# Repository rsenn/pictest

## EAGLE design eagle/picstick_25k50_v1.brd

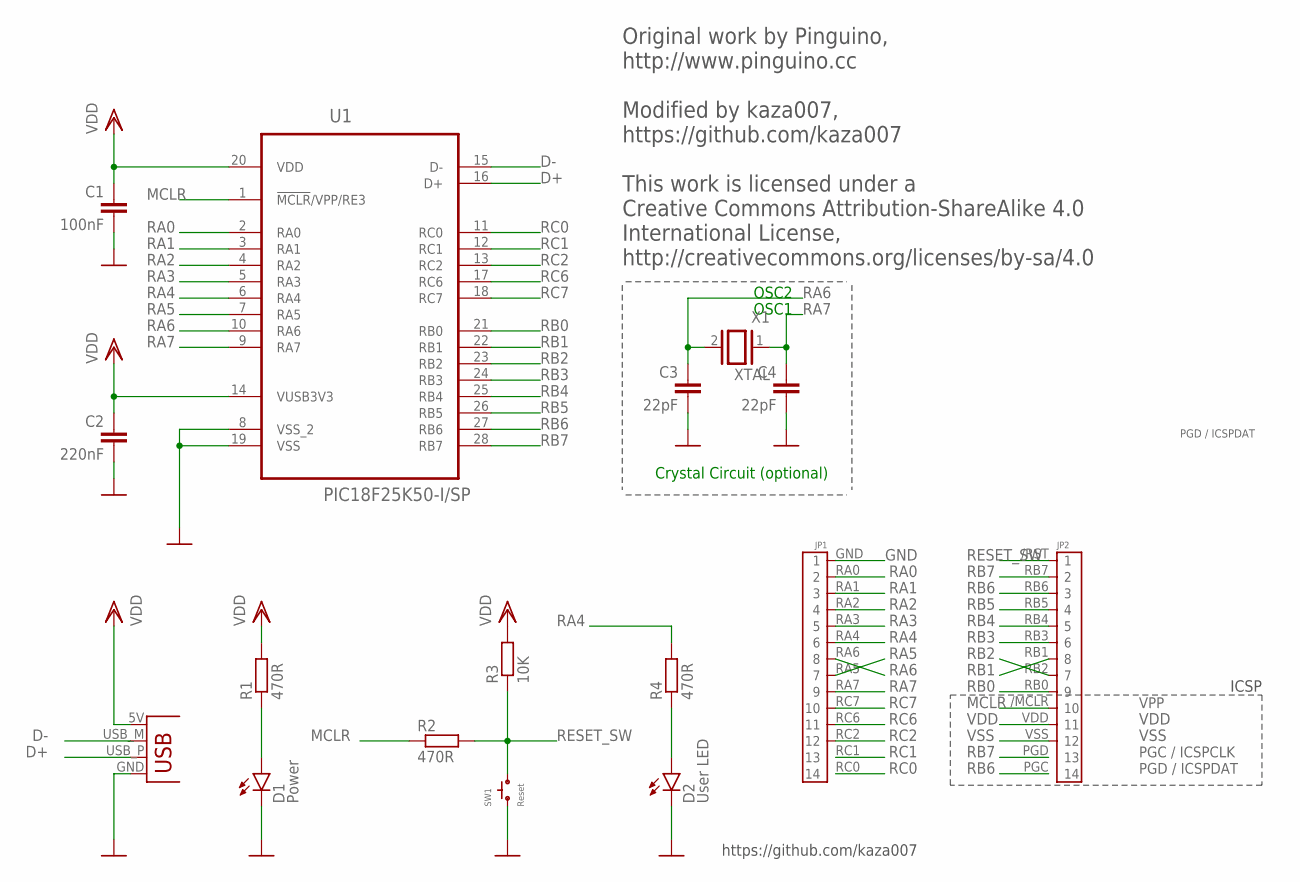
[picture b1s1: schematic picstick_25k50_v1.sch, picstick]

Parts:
C1: 100nF; C050-024X044
C2: 220nF; C050-024X044
C3, C4: 22pF; C025-024X044
D1: Power; LED3MM
D2: User LED; LED3MM
JP1: CONN-14P-PICSTICK-JP1; PICSTICK_JP1
JP2: CONN-14P-PICSTICK-JP2; PICSTICK_JP2
R1, R2, R4: 470R; 0204/7
R3: 10K; 0204/7
SW1: Reset; SKHLAAA010
U1: PIC18F25K50-I/SP; DIP254P762X406-28P
USB: FREETRONICS-MASTER-V1_USBPCB; FREETRONICS-MASTER-V1_USB-A-PCB
X1: XTAL; QS

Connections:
D+: U1.16 (D+), USB.USB_P (D+)
D-: U1.15 (D-), USB.USB_M (D-)
GND: C1.2, C2.2, C3.2, C4.2, D1.K (C), D2.K (C), JP1.GND (1), SW1.1, U1.8 (VSS_2), U1.19 (VSS), USB.GND
MCLR: JP2./MCLR (10), R2.1, U1.1 (!MCLR!/VPP/RE3)
unnamed: D1.A, R1.1
unnamed: D2.A, R4.1
RA0: JP1.RA0 (2), U1.2 (RA0)
RA1: JP1.RA1 (3), U1.3 (RA1)
RA2: JP1.RA2 (4), U1.4 (RA2)
RA3: JP1.RA3 (5), U1.5 (RA3)
RA4: JP1.RA4 (6), R4.2, U1.6 (RA4)
RA5: JP1.RA5 (7), U1.7 (RA5)
RA6: C3.1, JP1.RA6 (8), U1.10 (RA6), X1.2
RA7: C4.1, JP1.RA7 (9), U1.9 (RA7), X1.1
RB0: JP2.RB0 (9), U1.21 (RB0)
RB1: JP2.RB1 (8), U1.22 (RB1)
RB2: JP2.RB2 (7), U1.23 (RB2)
RB3: JP2.RB3 (6), U1.24 (RB3)
RB4: JP2.RB4 (5), U1.25 (RB4)
RB5: JP2.RB5 (4), U1.26 (RB5)
RB6: JP2.PGC (14), JP2.RB6 (3), U1.27 (RB6)
RB7: JP2.PGD (13), JP2.RB7 (2), U1.28 (RB7)
RC0: JP1.RC0 (14), U1.11 (RC0)
RC1: JP1.RC1 (13), U1.12 (RC1)
RC2: JP1.RC2 (12), U1.13 (RC2)
RC6: JP1.RC6 (11), U1.17 (RC6)
RC7: JP1.RC7 (10), U1.18 (RC7)
RESET_SW: JP2./RST (1), R2.2, R3.1, SW1.2
VDD: C1.1, C2.1, JP2.VDD (11), R1.2, R3.2, U1.14 (VUSB3V3), U1.20 (VDD), USB.5V (VBUS)
VSS: JP2.VSS (12)

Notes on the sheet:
ICSP
Crystal Circuit (optional)
OSC2
OSC1
https://github.com/kaza007
Original work by Pinguino, http://www.pinguino.cc Modified by kaza007, https://github.com/kaza007 This work is licensed under a Creative Commons Attribution-ShareAlike 4.0 International License, http://creativecommons.org/licenses/by-sa/4.0
PGD / ICSPDAT
PGC / ICSPCLK
VPP

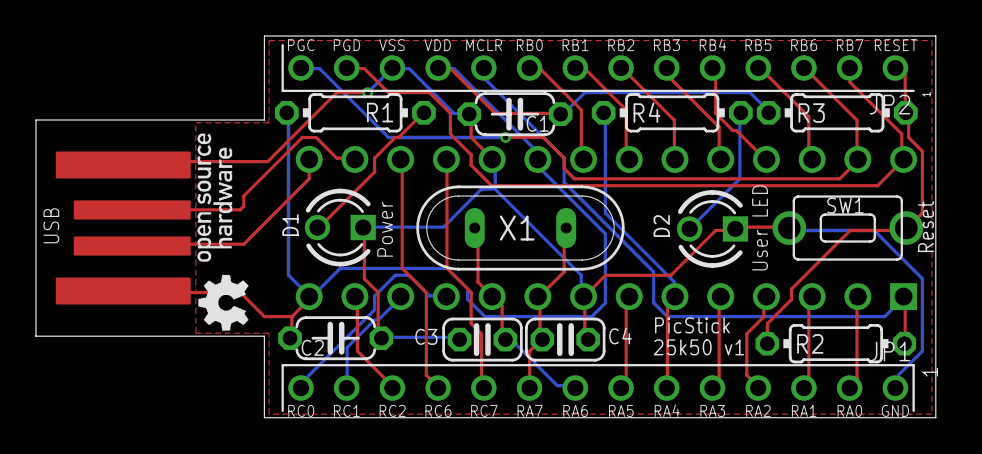
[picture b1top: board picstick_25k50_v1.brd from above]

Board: 2 copper layers, 50.0 x 21.2 mm, 16 parts (1 on the bottom side), 29 nets.

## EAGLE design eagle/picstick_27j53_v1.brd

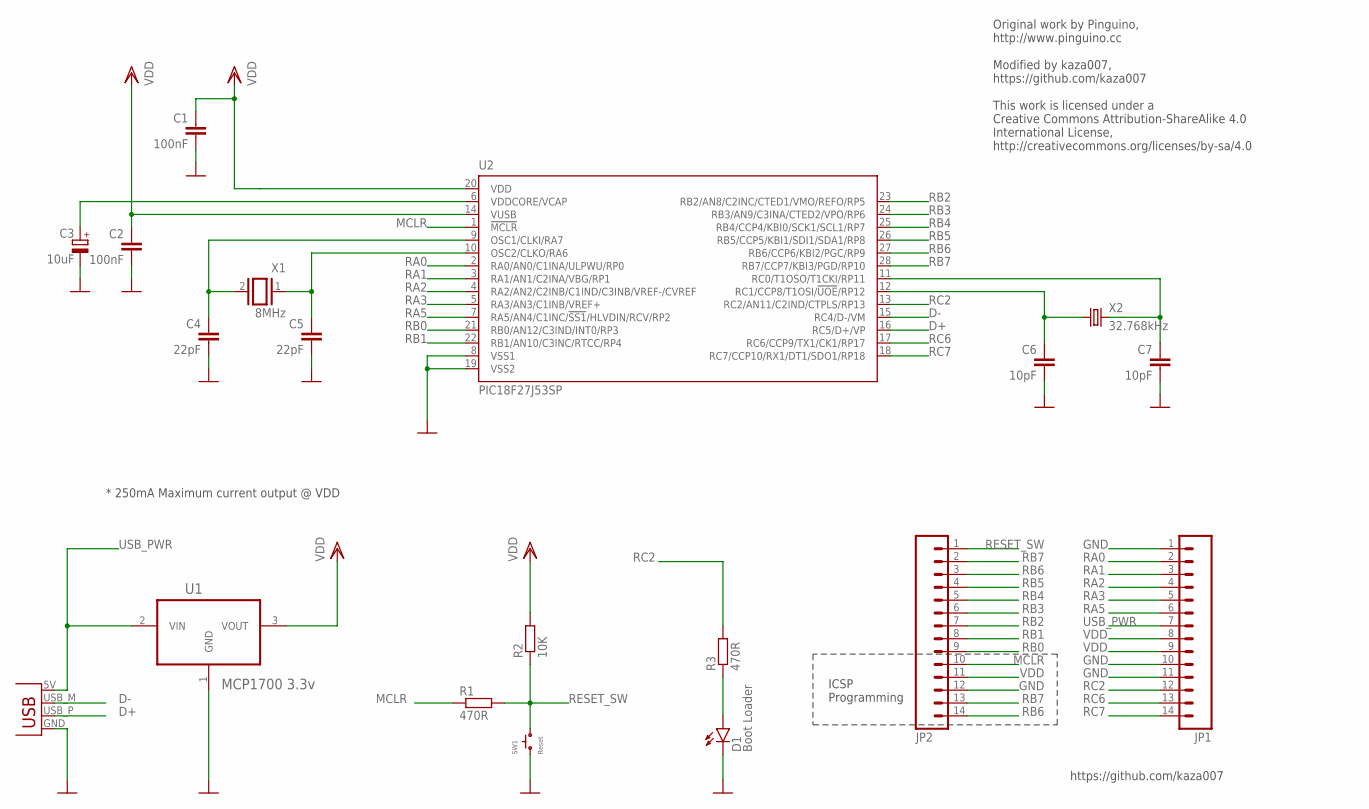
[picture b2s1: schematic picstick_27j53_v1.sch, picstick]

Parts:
C1, C2: 100nF; C050-024X044
C3: 10uF; E2,5-5
C4, C5: 22pF; C025-024X044
C6, C7: 10pF; C025-024X044
D1: Boot Loader; LED3MM
JP1, JP2: FREETRONICS-JON_M14; FREETRONICS-JON_1X14
R1, R3: 470R; 0204/7
R2: 10K; 0204/7
SW1: Reset; SKHLAAA010
U1: MCP1700 3.3v; TO127P254X495-3
U2: PIC18F27J53SP; DIL28-3
USB: FREETRONICS-MASTER-V1_USBPCB; FREETRONICS-MASTER-V1_USB-A-PCB
X1: 8MHz; QS
X2: 32.768kHz; TC26H

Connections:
D+: U2.16 (RC5/D+/VP), USB.USB_P (D+)
D-: U2.15 (RC4/D-/VM), USB.USB_M (D-)
GND: C1.2, C2.2, C3.-, C4.2, C5.2, C6.2, C7.2, D1.K (C), JP1.1, JP1.10, JP1.11, JP2.12, SW1.1, U1.1 (GND), U2.8 (VSS1), U2.19 (VSS2), USB.GND
MCLR: JP2.10, R1.1, U2.1 (!MCLR)
unnamed: C4.1, U2.9 (OSC1/CLKI/RA7), X1.2
unnamed: C5.1, U2.10 (OSC2/CLKO/RA6), X1.1
unnamed: C3.+, U2.6 (VDDCORE/VCAP)
unnamed: C7.1, U2.11 (RC0/T1OSO/T1CKI/RP11), X2.2
unnamed: C6.1, U2.12 (RC1/CCP8/T1OSI/!UOE!/RP12), X2.1
unnamed: D1.A, R3.1
RA0: JP1.2, U2.2 (RA0/AN0/C1INA/ULPWU/RP0)
RA1: JP1.3, U2.3 (RA1/AN1/C2INA/VBG/RP1)
RA2: JP1.4, U2.4 (RA2/AN2/C2INB/C1IND/C3INB/VREF-/CVREF)
RA3: JP1.5, U2.5 (RA3/AN3/C1INB/VREF+)
RA5: JP1.6, U2.7 (RA5/AN4/C1INC/!SS1!/HLVDIN/RCV/RP2)
RB0: JP2.9, U2.21 (RB0/AN12/C3IND/INT0/RP3)
RB1: JP2.8, U2.22 (RB1/AN10/C3INC/RTCC/RP4)
RB2: JP2.7, U2.23 (RB2/AN8/C2INC/CTED1/VMO/REFO/RP5)
RB3: JP2.6, U2.24 (RB3/AN9/C3INA/CTED2/VPO/RP6)
RB4: JP2.5, U2.25 (RB4/CCP4/KBI0/SCK1/SCL1/RP7)
RB5: JP2.4, U2.26 (RB5/CCP5/KBI1/SDI1/SDA1/RP8)
RB6: JP2.3, JP2.14, U2.27 (RB6/CCP6/KBI2/PGC/RP9)
RB7: JP2.2, JP2.13, U2.28 (RB7/CCP7/KBI3/PGD/RP10)
RC2: JP1.12, R3.2, U2.13 (RC2/AN11/C2IND/CTPLS/RP13)
RC6: JP1.13, U2.17 (RC6/CCP9/TX1/CK1/RP17)
RC7: JP1.14, U2.18 (RC7/CCP10/RX1/DT1/SDO1/RP18)
RESET_SW: JP2.1, R1.2, R2.1, SW1.2
USB_PWR: JP1.7, U1.2 (VIN), USB.5V (VBUS)
VDD: C1.1, C2.1, JP1.8, JP1.9, JP2.11, R2.2, U1.3 (VOUT), U2.14 (VUSB), U2.20 (VDD)

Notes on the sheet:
ICSP Programming
* 250mA Maximum current output @ VDD
https://github.com/kaza007
Original work by Pinguino, http://www.pinguino.cc Modified by kaza007, https://github.com/kaza007 This work is licensed under a Creative Commons Attribution-ShareAlike 4.0 International License, http://creativecommons.org/licenses/by-sa/4.0

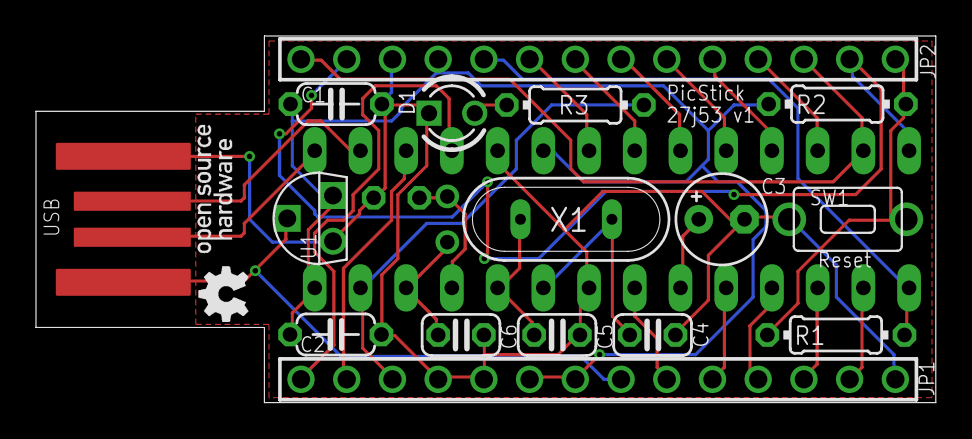
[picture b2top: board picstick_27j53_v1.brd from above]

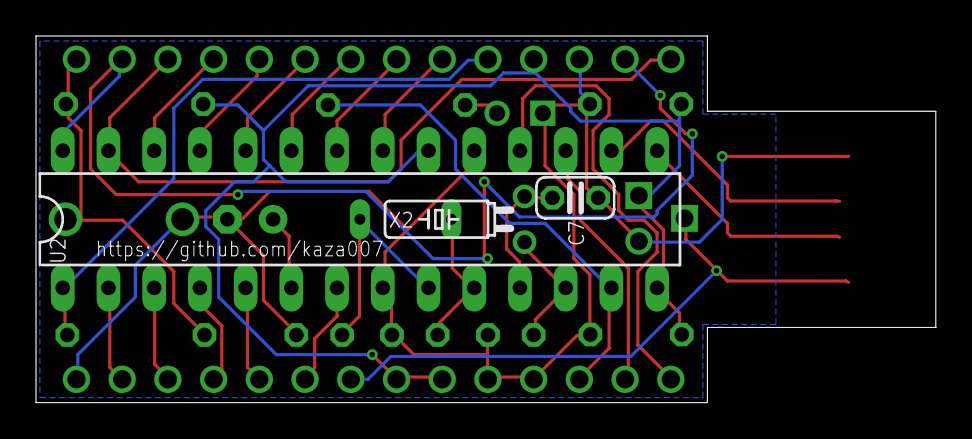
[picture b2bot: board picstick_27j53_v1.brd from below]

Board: 2 copper layers, 50.0 x 20.4 mm, 19 parts (3 on the bottom side), 29 nets.

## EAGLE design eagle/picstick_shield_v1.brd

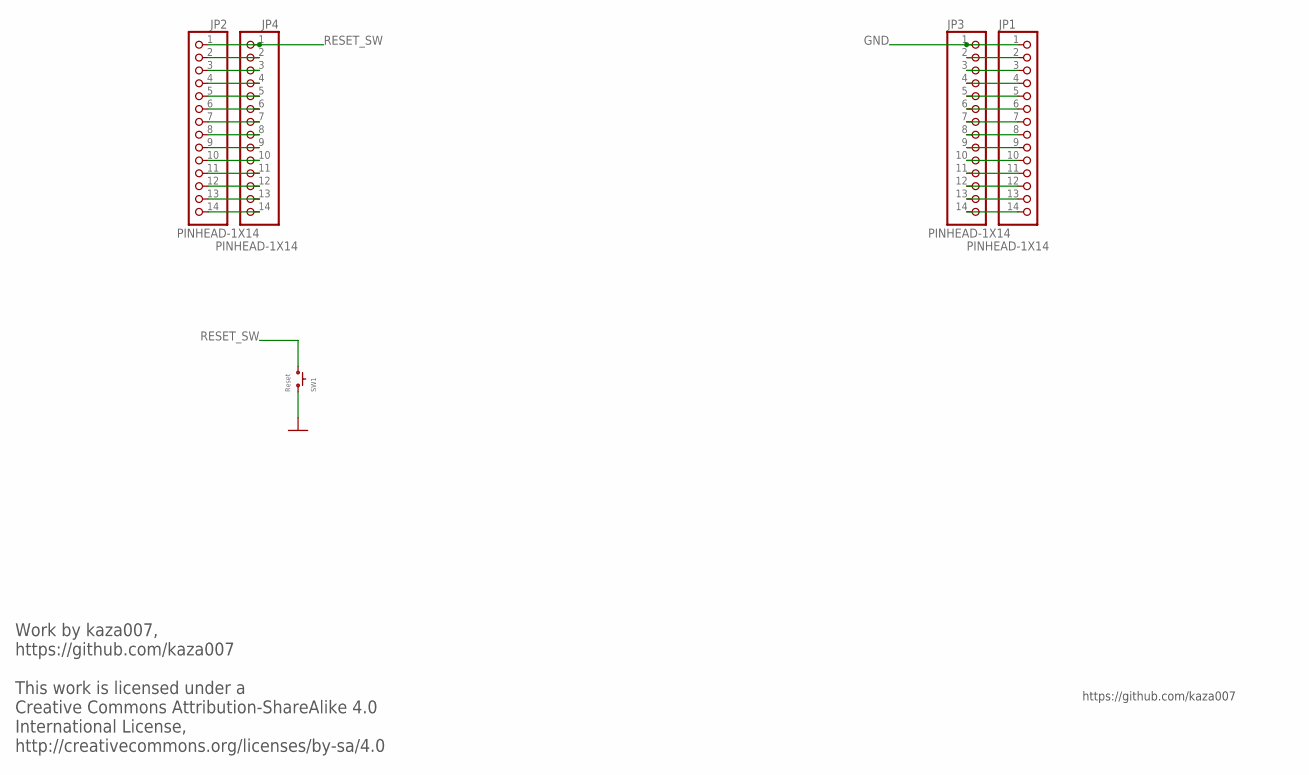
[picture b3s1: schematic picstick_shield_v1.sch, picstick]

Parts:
JP1, JP2, JP3, JP4: PINHEAD-1X14
SW1: Reset; SKHLAAA010

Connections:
GND: JP1.1, JP3.1, SW1.1
unnamed: JP1.2, JP3.2
unnamed: JP2.7, JP4.7
unnamed: JP2.8, JP4.8
unnamed: JP2.9, JP4.9
unnamed: JP2.10, JP4.10
unnamed: JP2.11, JP4.11
unnamed: JP2.12, JP4.12
unnamed: JP2.13, JP4.13
unnamed: JP2.14, JP4.14
unnamed: JP1.3, JP3.3
unnamed: JP1.4, JP3.4
unnamed: JP1.5, JP3.5
unnamed: JP1.6, JP3.6
unnamed: JP1.7, JP3.7
unnamed: JP1.8, JP3.8
unnamed: JP1.9, JP3.9
unnamed: JP1.10, JP3.10
unnamed: JP1.11, JP3.11
unnamed: JP1.12, JP3.12
unnamed: JP1.13, JP3.13
unnamed: JP1.14, JP3.14
RB2: JP2.6, JP4.6
RB3: JP2.5, JP4.5
RB4: JP2.4, JP4.4
RB5: JP2.3, JP4.3
RB6: JP2.2, JP4.2
RESET_SW: JP2.1, JP4.1, SW1.2

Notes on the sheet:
https://github.com/kaza007
Work by kaza007, https://github.com/kaza007 This work is licensed under a Creative Commons Attribution-ShareAlike 4.0 International License, http://creativecommons.org/licenses/by-sa/4.0

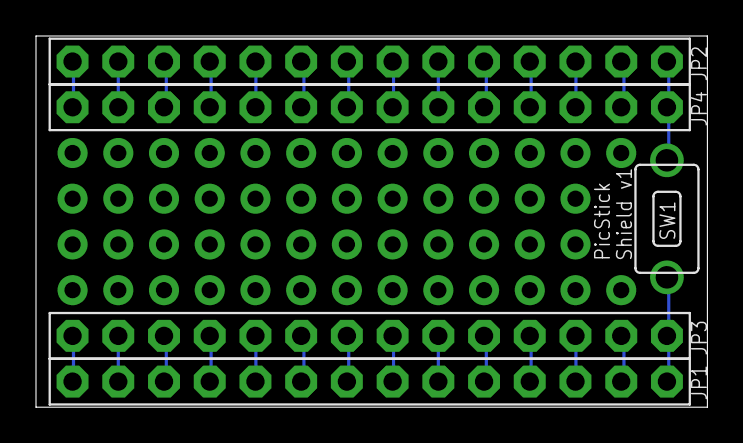
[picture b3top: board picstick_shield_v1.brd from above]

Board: 2 copper layers, 37.3 x 20.6 mm, 5 parts (0 on the bottom side), 28 nets.

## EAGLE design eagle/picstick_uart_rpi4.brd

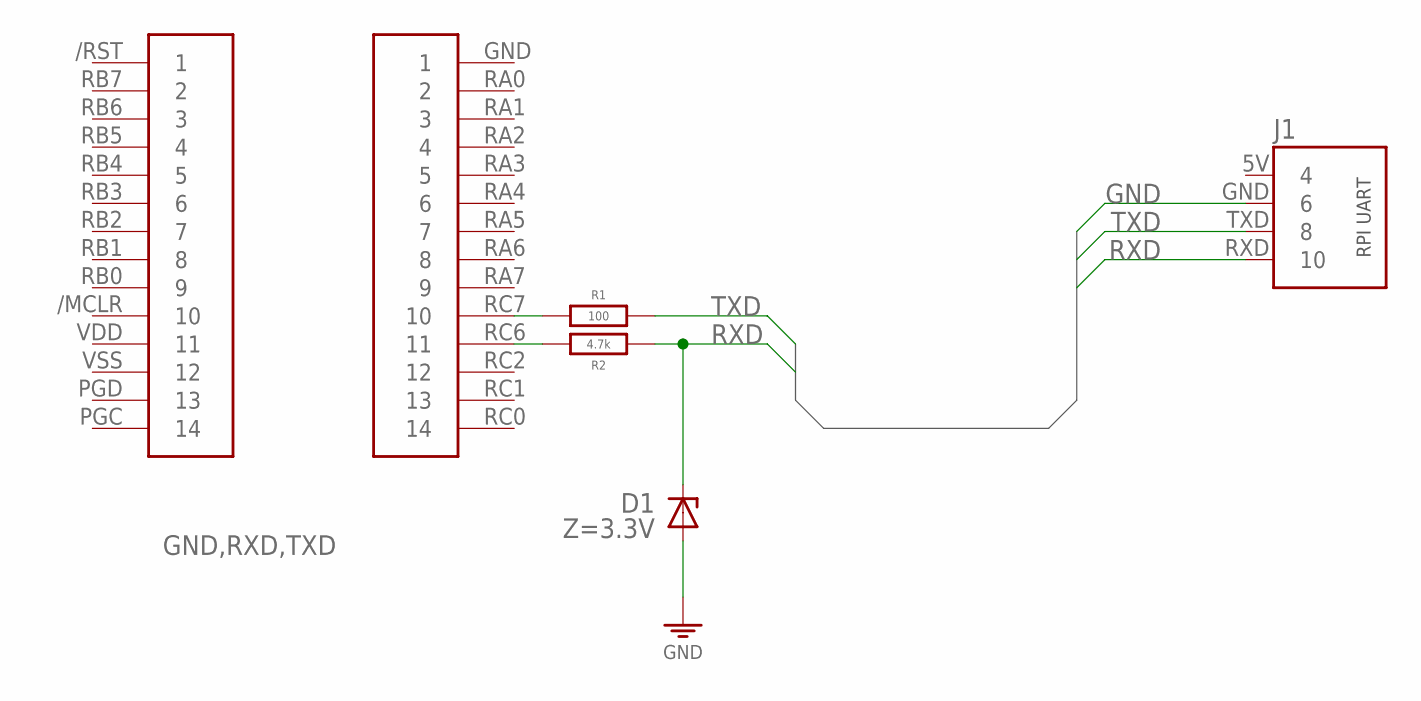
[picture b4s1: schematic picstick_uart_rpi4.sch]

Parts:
D1: Z=3.3V; DO34Z10
J1: RPI-UART-RPI4; RPI-UART
J2: PICSTICK; PICSTICK_ALT
R1: 100; 0204/12
R2: 4.7k; 0204/12

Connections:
GND: D1.A, J1.GND (6)
unnamed: J2.RC7 (10), R1.1
unnamed: J2.RC6 (11), R2.1
RXD: D1.C, J1.RXD (10), R2.2
TXD: J1.TXD (8), R1.2

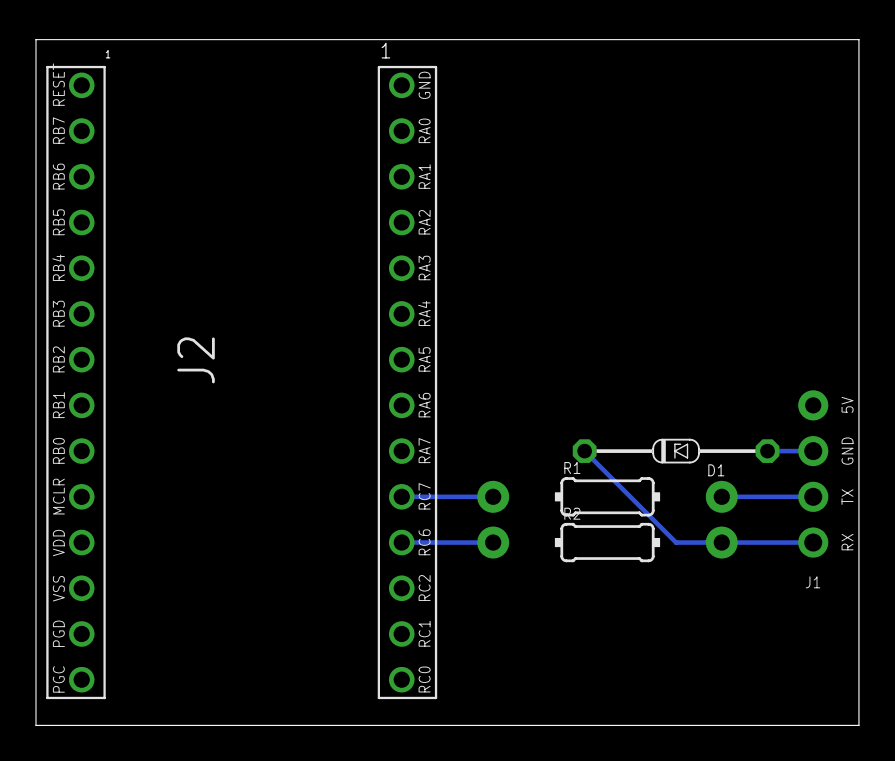
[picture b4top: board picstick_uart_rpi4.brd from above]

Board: 2 copper layers, 45.7 x 38.1 mm, 5 parts (0 on the bottom side), 5 nets.

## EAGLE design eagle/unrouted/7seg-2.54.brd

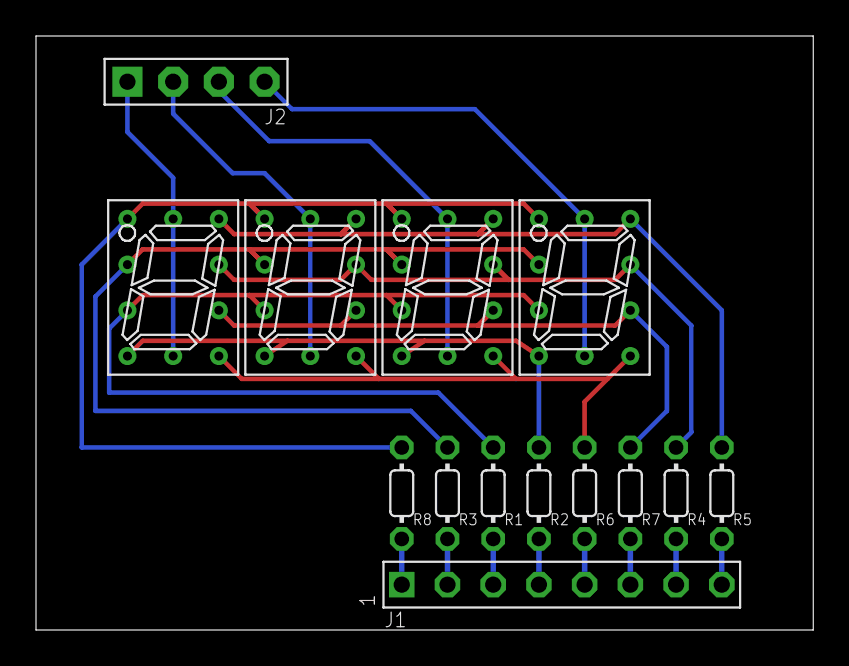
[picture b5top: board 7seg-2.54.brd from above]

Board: 2 copper layers, 43.2 x 33.0 mm, 14 parts (0 on the bottom side), 20 nets.

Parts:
J1: CONN-8P
J2: CONN-4P-4P; CONN-4P
R1, R2, R3, R4, R5, R6, R7, R8: 0202/5-V
U$1, U$2, U$3, U$4: TDSO1160-2.54; TDSX1150-2.54

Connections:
A: R1.2, U$1.7, U$2.7, U$3.7, U$4.7
B: R2.2, U$1.6, U$2.6, U$3.6, U$4.6
C: R3.2, U$1.4, U$2.4, U$3.4, U$4.4
C1: J2.1, U$1.3, U$1.8
C2: J2.2, U$2.3, U$2.8
C3: J2.3, U$3.3, U$3.8
C4: J2.4, U$4.3, U$4.8
D: R4.2, U$1.2, U$2.2, U$3.2, U$4.2
DP: R8.2, U$1.5, U$2.5, U$3.5, U$4.5
E: R5.2, U$1.1, U$2.1, U$3.1, U$4.1
F: R6.2, U$1.10, U$2.10, U$3.10, U$4.10
G: R7.2, U$1.9, U$2.9, U$3.9, U$4.9
_A: J1.3, R1.1
_B: J1.4, R2.1
_C: J1.2, R3.1
_D: J1.7, R4.1
_DP: J1.1, R8.1
_E: J1.8, R5.1
_F: J1.5, R6.1
_G: J1.6, R7.1

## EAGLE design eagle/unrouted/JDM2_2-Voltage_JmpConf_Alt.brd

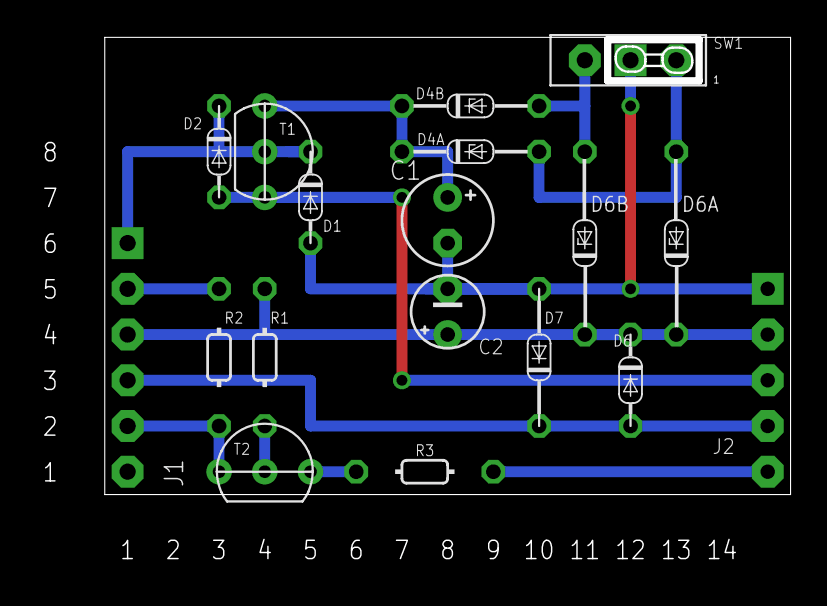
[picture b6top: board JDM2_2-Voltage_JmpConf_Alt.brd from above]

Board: 2 copper layers, 38.1 x 25.4 mm, 18 parts (0 on the bottom side), 13 nets.

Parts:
C1: 100uF; E2,5-5/V
C2: 22uF; E2.5-4/V
D1, D6: 1N4148; DO34-5V
D2: 1N4148; DO34-5
D4A: Z=8.1v; DO34Z7
D4B: Z=13.8V; DO34Z7
D6A: Z=3.3V; DO34Z10V
D6B: Z=5.1V; DO34Z10V
D7: 1N4148; DO34-7V
J1: COMPORT-6PIN; RS232-6PIN
J2: PIC-ICSPICSP; PIC-ICSP
R1: 10k; 0202/7-V
R2: 1.5k; 0202/7-V
R3: 100; 0202/7
SW1: SL-SW-1P-2T-JPSW; JPSW-1P2T
T1, T2: BC547; TO92-CBE

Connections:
/MCLR: D2.A, J2.3, T1.E
CLK: D6.A, D7.C, J1.4, J2.4
CTS: J1.5, R2.1, T2.C
DATA: R3.2, T2.E
GND: C1.-, C2.-, D1.A, D7.A, J2.1, SW1.P
unnamed: R1.1, T2.B
unnamed: D4A.A, D6A.A, SW1.O
unnamed: D4B.A, D6B.A, SW1.S
unnamed: J1.2, R2.2
PGD: J2.5, R3.1
TXD: D1.C, D2.C, J1.1, T1.B
VCC: C2.+, D6.C, D6A.C, D6B.C, J1.3, J2.2, R1.2
VPP: C1.+, D4A.C, D4B.C, T1.C
